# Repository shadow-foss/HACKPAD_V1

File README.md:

# HACKPAD

Hackpad is a DIY wireless,repairable and modular gamepad.

the aim of the project is to make a easy to build customisable/hack-able gamepad

its powered by a esp32

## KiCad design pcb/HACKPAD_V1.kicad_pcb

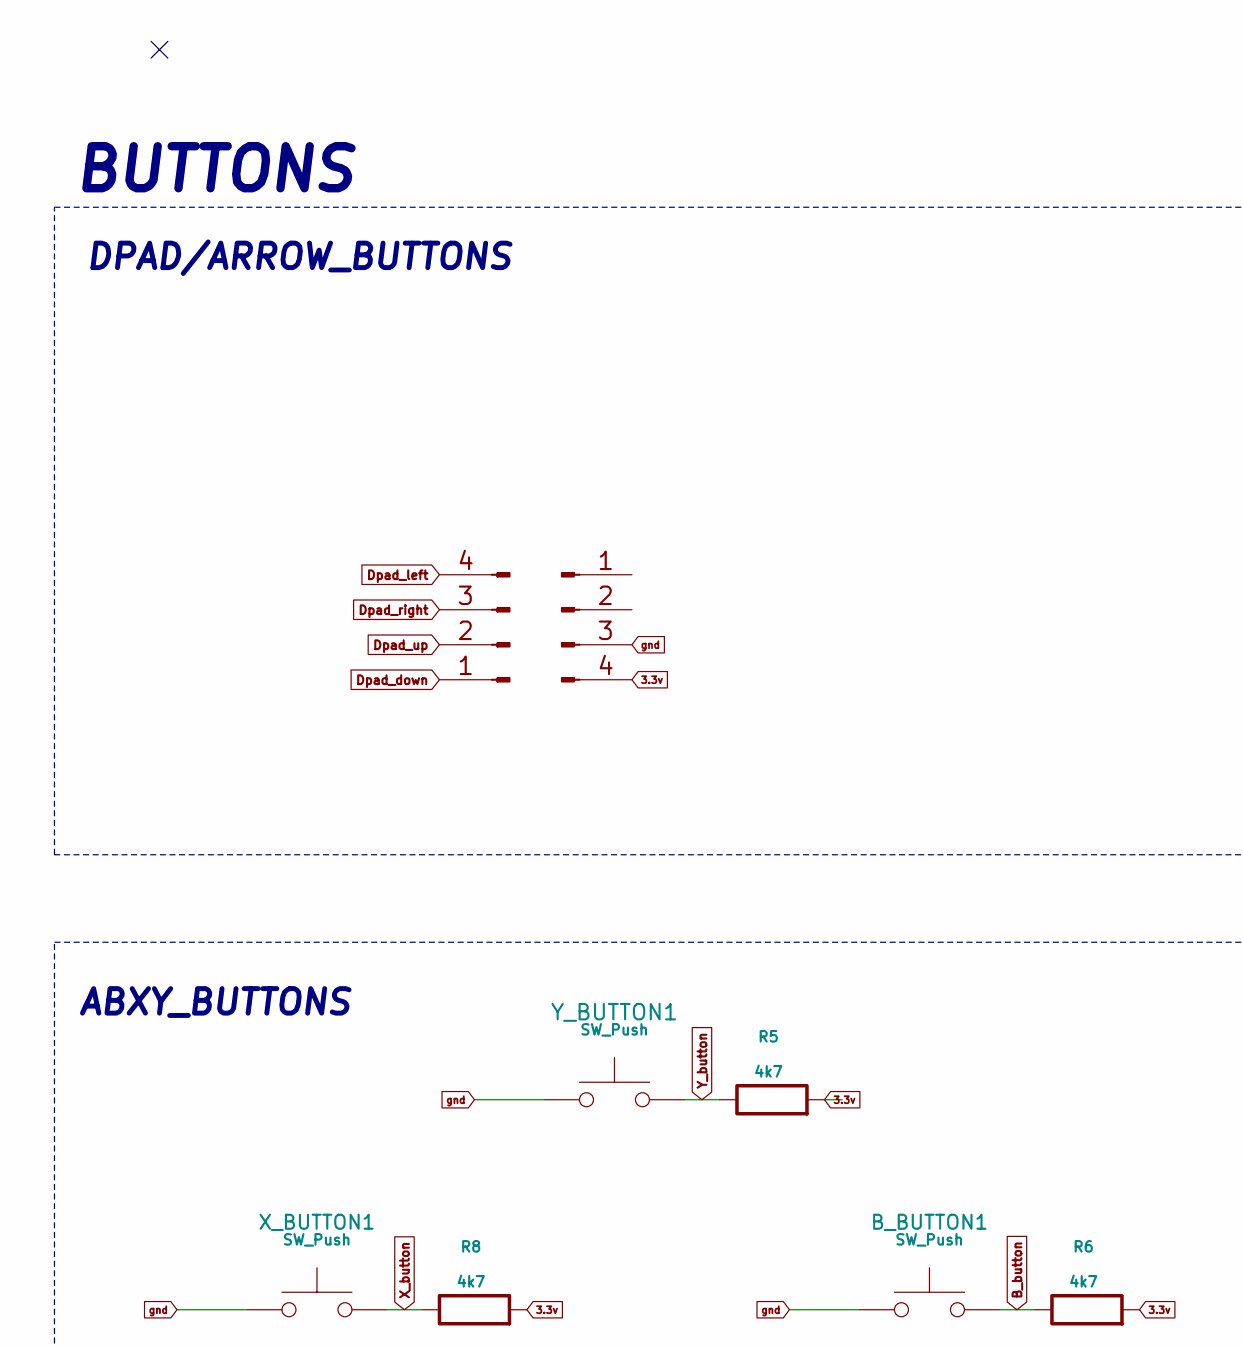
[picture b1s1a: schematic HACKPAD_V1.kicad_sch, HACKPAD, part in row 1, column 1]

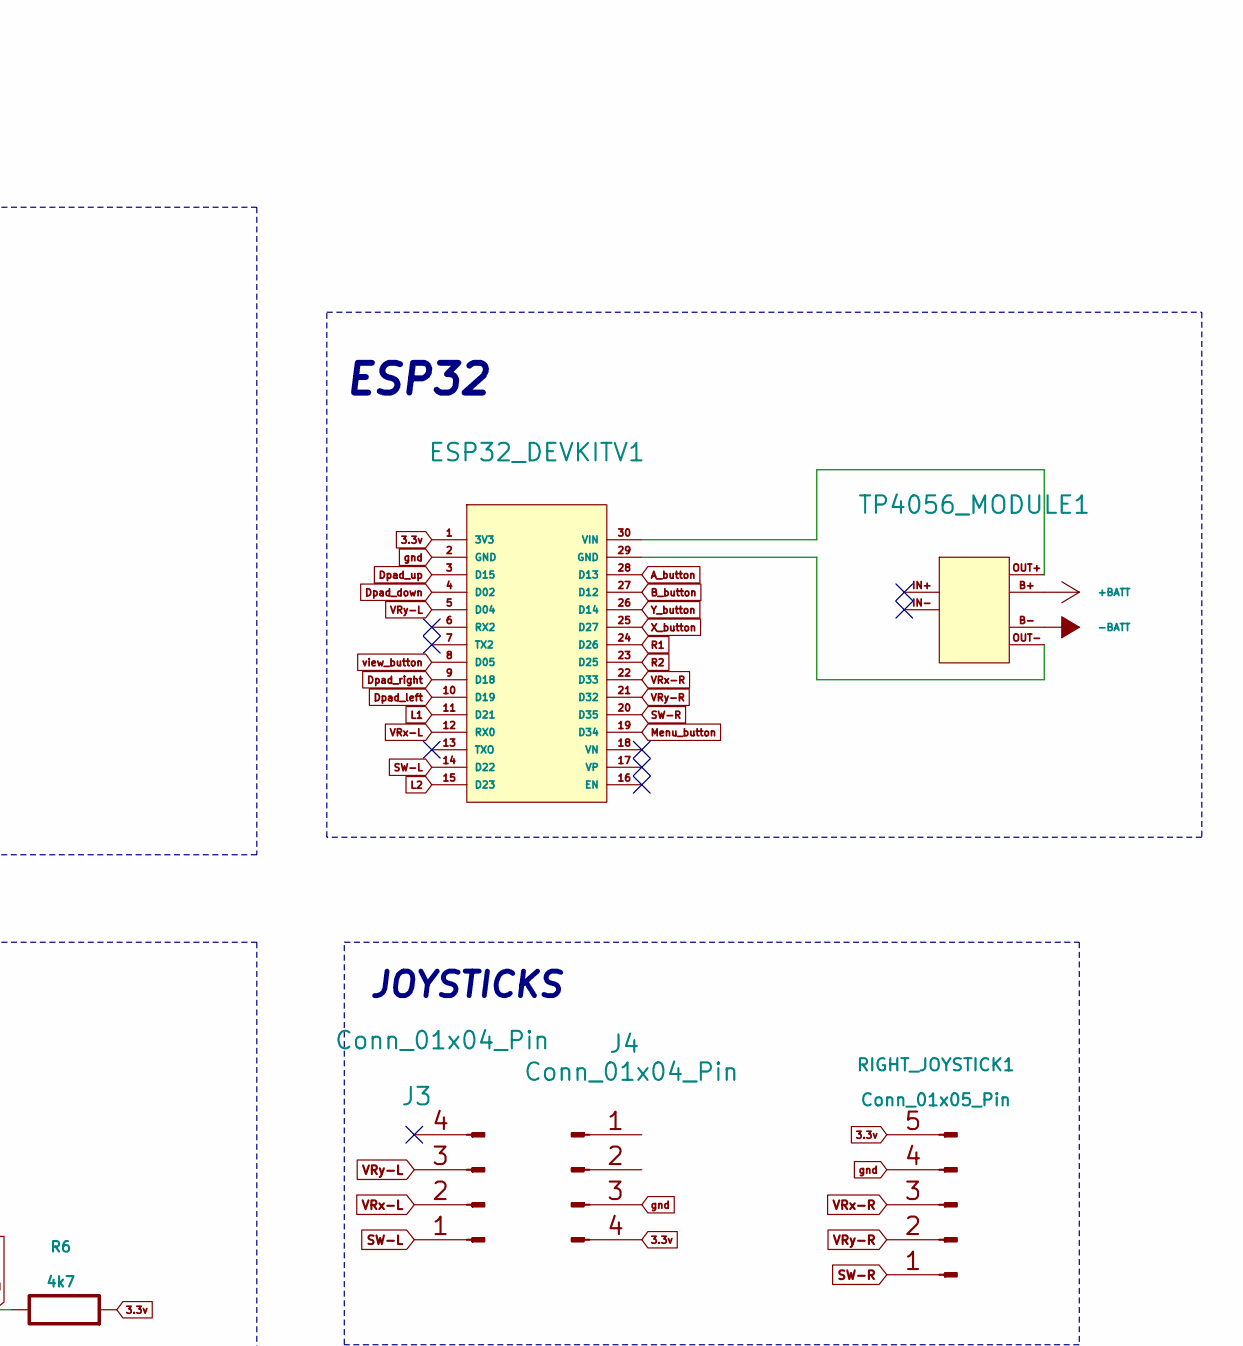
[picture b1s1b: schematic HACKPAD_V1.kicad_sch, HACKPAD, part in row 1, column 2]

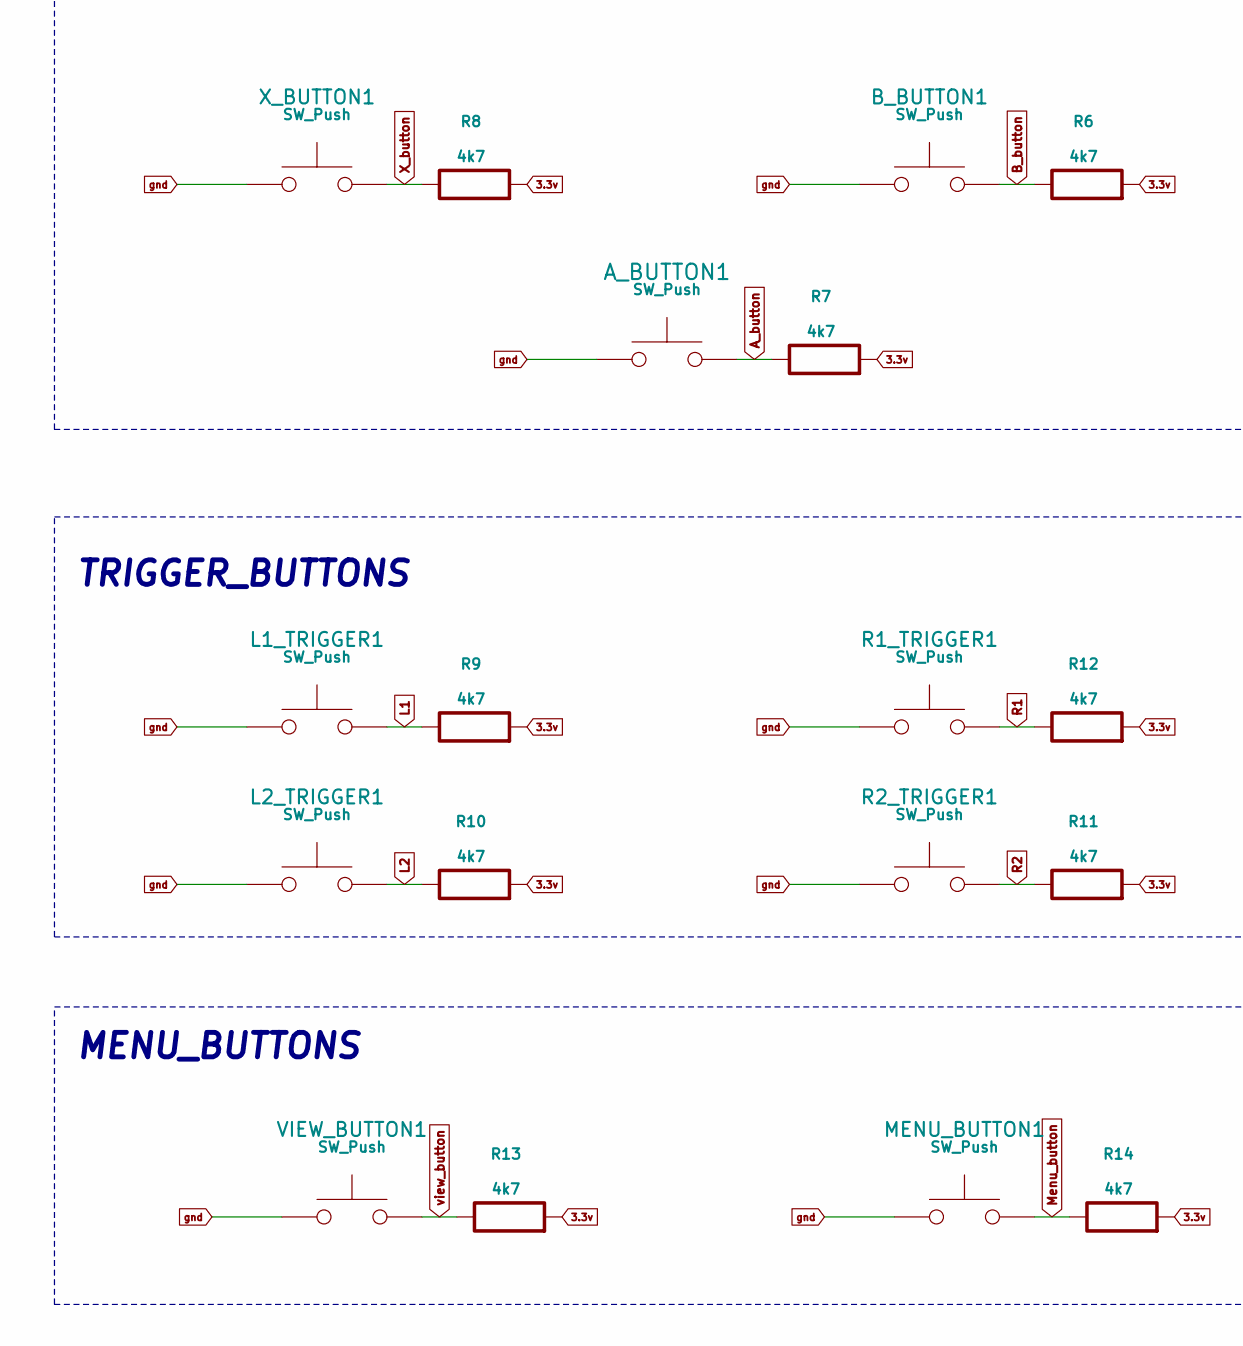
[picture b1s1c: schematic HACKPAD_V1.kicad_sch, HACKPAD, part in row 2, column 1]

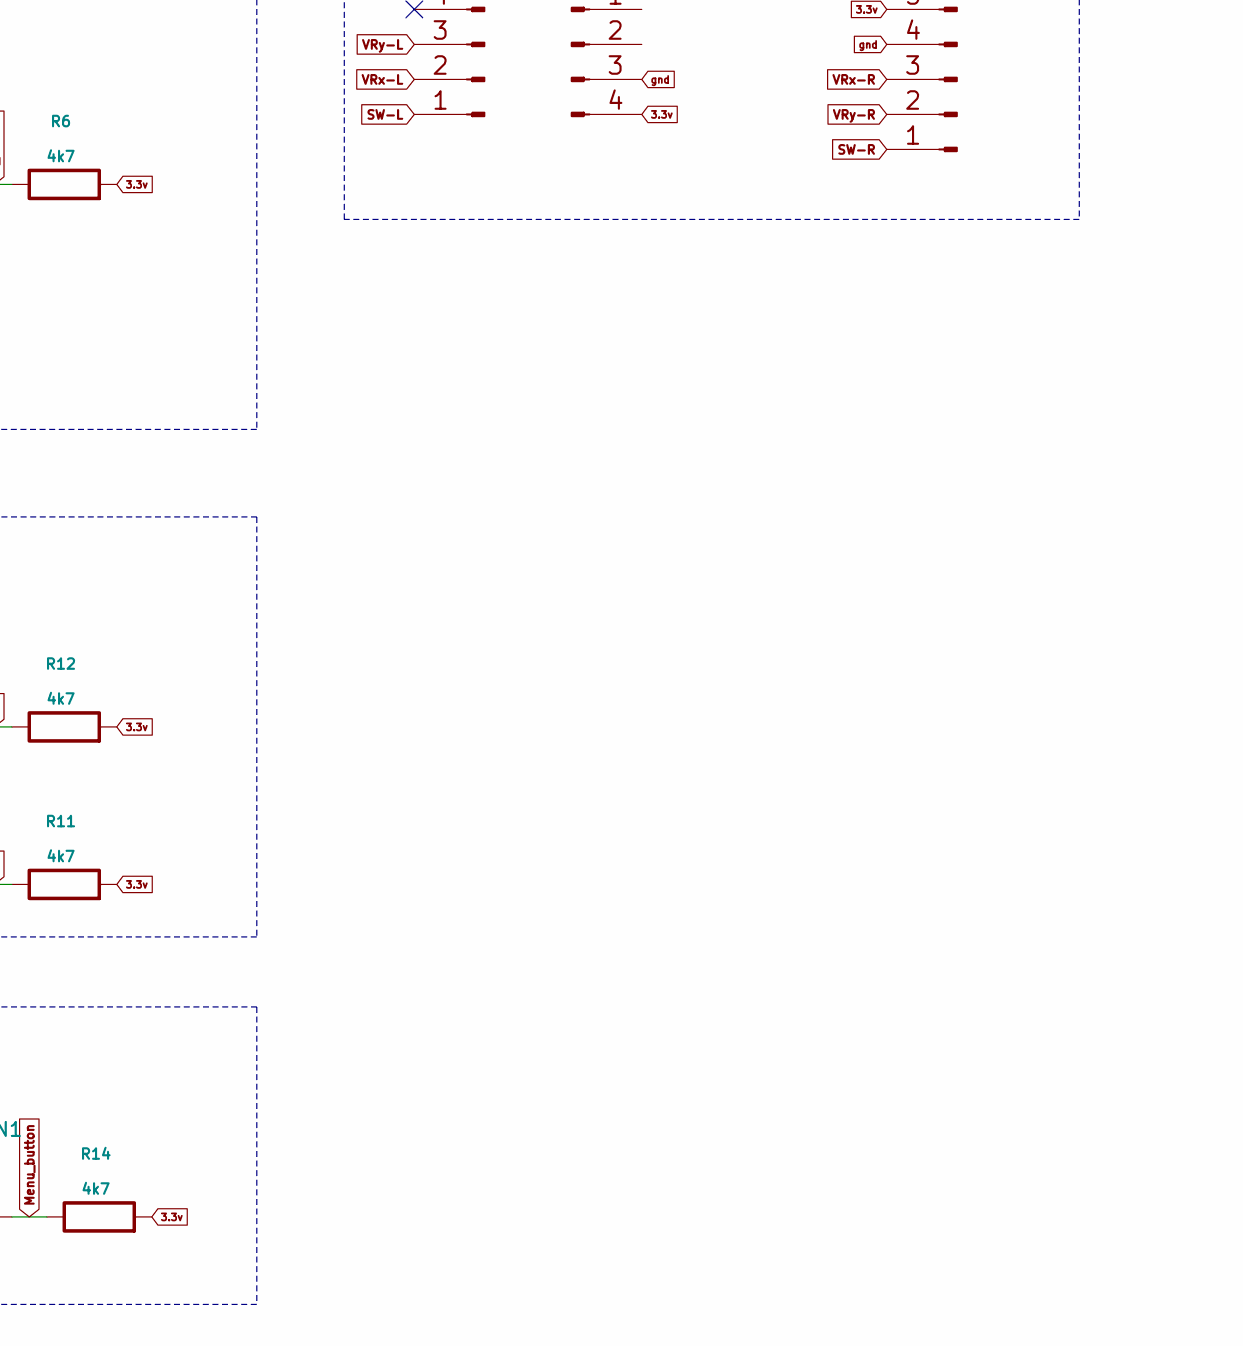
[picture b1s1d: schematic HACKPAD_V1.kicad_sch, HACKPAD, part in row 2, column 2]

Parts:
A_BUTTON1: SW_Push; SW_PUSH-12mm
B_BUTTON1: SW_Push; SW_PUSH-12mm
ESP32_DEVKITV1: ESP32_DEVKITV1
J1, J2, J3, J4: Conn_01x04_Pin; PinHeader_1x04_P2.54mm_Vertical
L1_TRIGGER1, L2_TRIGGER1: SW_Push; PinHeader_1x02_P2.54mm_Vertical
MENU_BUTTON1: SW_Push; SW_PUSH-12mm
R1_TRIGGER1, R2_TRIGGER1: SW_Push; PinHeader_1x02_P2.54mm_Vertical
R5, R6, R7, R8, R9, R10, R11, R12, R13, R14: 4k7; R_1206_3216Metric_Pad1.30x1.75mm_HandSolder
RIGHT_JOYSTICK1: Conn_01x05_Pin; PinSocket_1x05_P2.54mm_Vertical
TP4056_MODULE1: TP4056
VIEW_BUTTON1: SW_Push; SW_PUSH-12mm
X_BUTTON1: SW_Push; SW_PUSH-12mm
Y_BUTTON1: SW_Push; SW_PUSH-12mm

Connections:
3.3v: ESP32_DEVKITV1.1 (3V3), J1.4, J4.4, R5.2, R6.2, R7.2, R8.2, R9.2, R10.2, R11.2, R12.2, R13.2, R14.2, RIGHT_JOYSTICK1.5
+BATT: TP4056_MODULE1.B+
-BATT: TP4056_MODULE1.B-
A_button: A_BUTTON1.2, ESP32_DEVKITV1.28 (D13), R7.1
B_button: B_BUTTON1.2, ESP32_DEVKITV1.27 (D12), R6.1
Dpad_down: ESP32_DEVKITV1.4 (D02), J2.1
Dpad_left: ESP32_DEVKITV1.10 (D19), J2.4
Dpad_right: ESP32_DEVKITV1.9 (D18), J2.3
Dpad_up: ESP32_DEVKITV1.3 (D15), J2.2
L1: ESP32_DEVKITV1.11 (D21), L1_TRIGGER1.2, R9.1
L2: ESP32_DEVKITV1.15 (D23), L2_TRIGGER1.2, R10.1
Menu_button: ESP32_DEVKITV1.19 (D34), MENU_BUTTON1.2, R14.1
unnamed: ESP32_DEVKITV1.29 (GND), TP4056_MODULE1.OUT-
unnamed: ESP32_DEVKITV1.30 (VIN), TP4056_MODULE1.OUT+
R1: ESP32_DEVKITV1.24 (D26), R1_TRIGGER1.2, R12.1
R2: ESP32_DEVKITV1.23 (D25), R2_TRIGGER1.2, R11.1
SW-L: ESP32_DEVKITV1.14 (D22), J3.1
SW-R: ESP32_DEVKITV1.20 (D35), RIGHT_JOYSTICK1.1
VRx-L: ESP32_DEVKITV1.12 (RX0), J3.2
VRx-R: ESP32_DEVKITV1.22 (D33), RIGHT_JOYSTICK1.3
VRy-L: ESP32_DEVKITV1.5 (D04), J3.3
VRy-R: ESP32_DEVKITV1.21 (D32), RIGHT_JOYSTICK1.2
X_button: ESP32_DEVKITV1.25 (D27), R8.1, X_BUTTON1.2
Y_button: ESP32_DEVKITV1.26 (D14), R5.1, Y_BUTTON1.2
gnd: A_BUTTON1.1, B_BUTTON1.1, ESP32_DEVKITV1.2 (GND), J1.3, J4.3, L1_TRIGGER1.1, L2_TRIGGER1.1, MENU_BUTTON1.1, R1_TRIGGER1.1, R2_TRIGGER1.1, RIGHT_JOYSTICK1.4, VIEW_BUTTON1.1, X_BUTTON1.1, Y_BUTTON1.1
view_button: ESP32_DEVKITV1.8 (D05), R13.1, VIEW_BUTTON1.2

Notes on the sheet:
ESP32
ABXY_BUTTONS
MENU_BUTTONS
DPAD/ARROW_BUTTONS
TRIGGER_BUTTONS
BUTTONS
JOYSTICKS

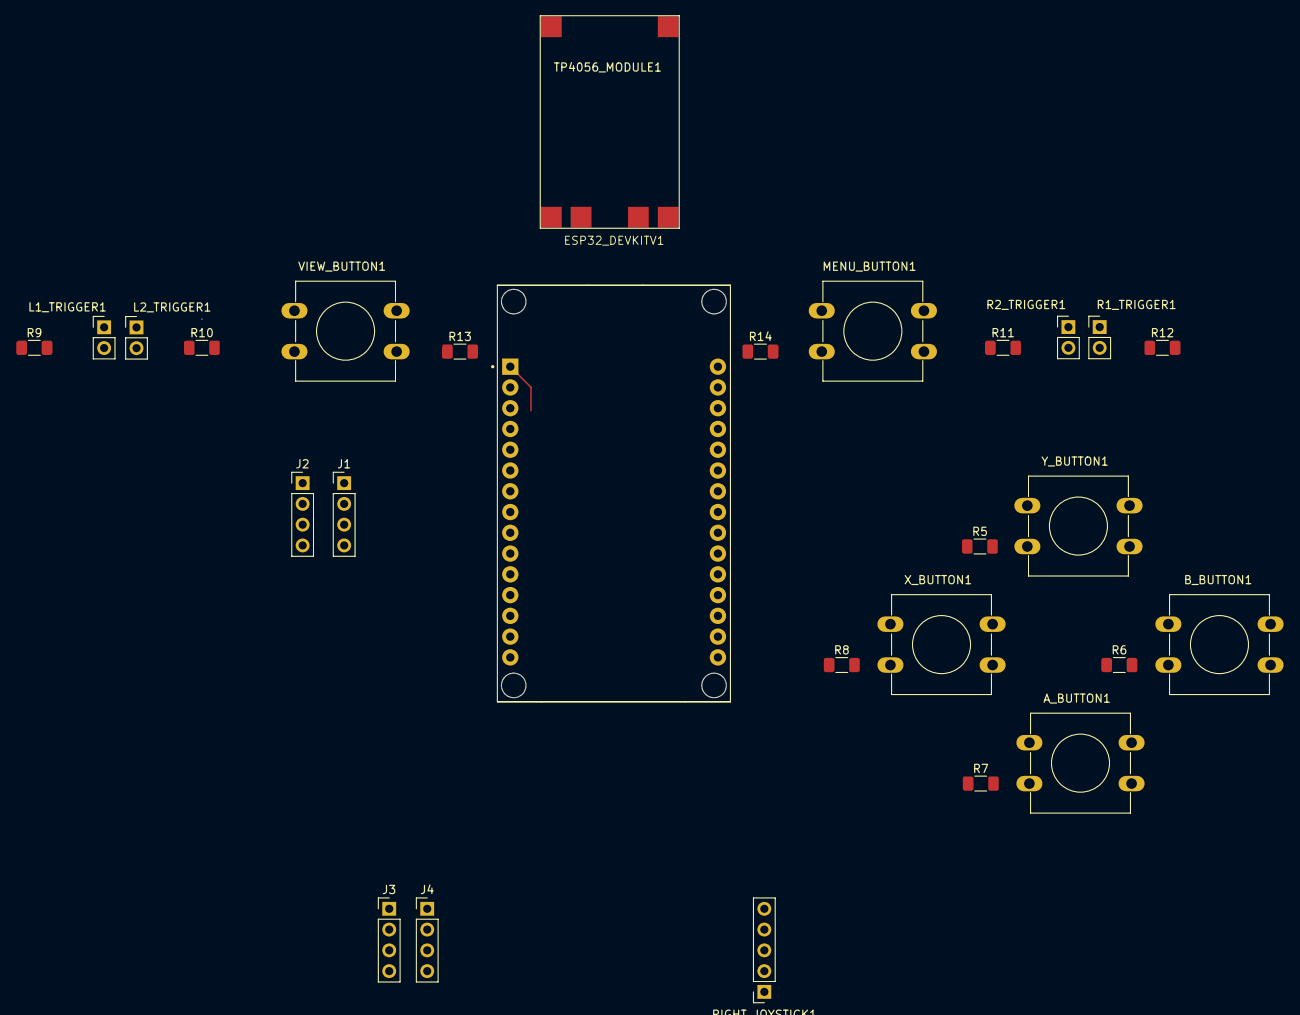
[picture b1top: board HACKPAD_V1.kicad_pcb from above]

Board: 2 copper layers, 27 parts (0 on the bottom side), 24 nets.

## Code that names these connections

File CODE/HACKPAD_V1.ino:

/*
 * ANDROID GAMEPAD
 * {A=1, B=2, C=3, X=4, Y=5, Z=6, L1=7, R1=8, L2=9, R2=10,
 * Select=11, Start=12, PS=13, L3=14, R3=15, UP=16, DOWN=17, RIGHT=18, LEFT=19} 
 * 
 * PS GAMEPAD MODE
 * {SQUARE=1, X=2, CIRCLE=3, TRIANGLE=4, L1=5, R1=6, L2=7, R2=8,
 * Select=9, Start=10, L3=11, R3=12, PS=13, UP=16, DOWN=17, RIGHT=18, LEFT=19}
 * 
 */

#include <Arduino.h>
#include <BleGamepad.h>


//ABXY BUTTONS
#define X_BUTTON 13         // A
#define CIRCLE_BUTTON 12    // B
#define TRIANGLE_BUTTON 14  // Y
#define SQUARE_BUTTON 27    // X
#define UP_BUTTON 15        // UP
#define DOWN_BUTTON 2       // DOWN
#define RIGHT_BUTTON 18     // RIGHT
#define LEFT_BUTTON 19      // LEFT
//TRIGGERS
#define R1_BUTTON 26
#define R2_BUTTON 25
#define L1_BUTTON 21
#define L2_BUTTON 23

//MENU BUTTONS
#define VIEW_BUTTON 16
#define MENU_BUTTON 34

//JOYSTICKS BUTTONS
#define R3_BUTTON 35
#define L3_BUTTON 22

//JOYSTICKS
#define LEFT_VRX_JOYSTICK 5
#define LEFT_VRY_JOYSTICK 4
#define RIGHT_VRX_JOYSTICK 33
#define RIGHT_VRY_JOYSTICK 32

#define NUM_BUTTONS 17

//The order of these three arrays matters a lot, be carefully when changing them
int buttonsPins[NUM_BUTTONS] = {X_BUTTON, CIRCLE_BUTTON, TRIANGLE_BUTTON, SQUARE_BUTTON,
                          R1_BUTTON, R2_BUTTON, L1_BUTTON, L2_BUTTON,
                          VIEW_BUTTON, MENU_BUTTON,
                          R3_BUTTON, L3_BUTTON, UP_BUTTON,
                          DOWN_BUTTON, RIGHT_BUTTON, LEFT_BUTTON};

//There is not buttons for Y and Z
int androidGamepadButtons[NUM_BUTTONS] = {1, 2, 3, 4, 8, 10, 7, 9, 12, 11, 13, 15, 14, 16, 17, 18, 19};
int PS1GamepadButtons[NUM_BUTTONS] = {2, 3, 4, 1, 6, 8, 5, 7, 10, 9, 13, 12, 11, 16, 17, 18, 19};
int PCGamepadButtons[NUM_BUTTONS] = {1, 2, 4, 3, 6, 8, 5, 7, 10, 9, 0, 12, 11, 16, 17, 18, 19};


uint16_t leftVrxJoystickLecture = 0;
uint16_t leftVryJoystickLecture = 0;
uint16_t rightVrxJoystickLecture = 0;
uint16_t rightVryJoystickLecture = 0;

uint16_t leftVrxJoystickValue = 0;
uint16_t leftVryJoystickValue = 0;
uint16_t rightVrxJoystickValue = 0;
uint16_t rightVryJoystickValue = 0;



typedef enum{ANDROID, PS1, PC} GamepadModes;
GamepadModes gamepadMode = ANDROID;


BleGamepad bleGamepad("Hackpad", "Hackpad Home");
BleGamepadConfiguration bleGamepadConfig;  


void setup() {
  // put your setup code here, to run once:
  delay(1000);
  Serial.begin(115200);

  for(int i=0; i<NUM_BUTTONS; i++){
    pinMode(buttonsPins[i], INPUT_PULLUP);
  }

  bleGamepadConfig.setAutoReport(false);
  bleGamepadConfig.setControllerType(CONTROLLER_TYPE_GAMEPAD); // CONTROLLER_TYPE_JOYSTICK, CONTROLLER_TYPE_GAMEPAD (DEFAULT), CONTROLLER_TYPE_MULTI_AXIS
  bleGamepadConfig.setVid(0xe502);
  bleGamepadConfig.setPid(0xabcd);
  bleGamepadConfig.setHatSwitchCount(4);
  bleGamepad.begin(&bleGamepadConfig);
}

void loop() {
  // put your main code here, to run repeatedly:
  if(bleGamepad.isConnected()){
    //Joysticks lecture
    leftVrxJoystickLecture = analogRead(LEFT_VRX_JOYSTICK);
    leftVryJoystickLecture = analogRead(LEFT_VRY_JOYSTICK);
    rightVrxJoystickLecture = analogRead(RIGHT_VRX_JOYSTICK);
    rightVryJoystickLecture = analogRead(RIGHT_VRY_JOYSTICK);

    //Compute joysticks value
    leftVrxJoystickValue = map(leftVrxJoystickLecture, 4095, 0, 0, 32737);
    leftVryJoystickValue = map(leftVryJoystickLecture, 0, 4095, 0, 32737);
    rightVrxJoystickValue = map(rightVrxJoystickLecture, 4095, 0, 0, 32737);
    rightVryJoystickValue = map(rightVryJoystickLecture, 0, 4095, 0, 32737);

    
    switch(gamepadMode){
      case ANDROID:
        for(int i=0; i<NUM_BUTTONS; i++){
          if(!digitalRead(buttonsPins[i])){
              bleGamepad.press(androidGamepadButtons[i]);   
          }
          else{
              bleGamepad.release(androidGamepadButtons[i]);     
          }
          joysticksHandlerForMobile(leftVrxJoystickValue, leftVryJoystickValue, rightVrxJoystickValue, rightVryJoystickValue);
        } 
        break;
      case PS1:
        for(int i=0; i<NUM_BUTTONS; i++){
          if(!digitalRead(buttonsPins[i])){
            bleGamepad.press(PS1GamepadButtons[i]);     
          }
          else{
            bleGamepad.release(PS1GamepadButtons[i]);      
          }
          joysticksHandlerForMobile(leftVrxJoystickValue, leftVryJoystickValue, rightVrxJoystickValue, rightVryJoystickValue);
        } 
        break;

        case PC:
          for(int i=0; i<NUM_BUTTONS; i++){
            if(!digitalRead(buttonsPins[i])){
              bleGamepad.press(PCGamepadButtons[i]);
            }
            else{
              bleGamepad.release(PCGamepadButtons[i]);
            }
            joysticksHandlerForPC(leftVrxJoystickValue, leftVryJoystickValue, rightVrxJoystickValue, rightVryJoystickValue);
          }
          break;
    }

    bleGamepad.sendReport();
  }
}

void joysticksHandlerForMobile(uint16_t leftVrx, uint16_t leftVry, uint16_t rightVrx, uint16_t rightVry){
  bleGamepad.setLeftThumb(leftVrx, leftVryJoystickValue);
  bleGamepad.setRightThumb(rightVrxJoystickValue, rightVryJoystickValue);  
}

void joysticksHandlerForPC(uint16_t leftVrx, uint16_t leftVry, uint16_t rightVrx, uint16_t rightVry){
  bleGamepad.setX(leftVrxJoystickValue);
  bleGamepad.setY(leftVryJoystickValue);
  bleGamepad.setZ(rightVrxJoystickValue);
  bleGamepad.setRX(rightVryJoystickValue);
}

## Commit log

2024-06-20 schematics
2024-06-30 LICENSE
2024-06-30 Create LICENSE
2024-06-30 Delete
2024-07-06 pcb update
2024-07-06 updated pcb
2024-07-20 symbols and footprint
2024-07-21 ADDED CODE
